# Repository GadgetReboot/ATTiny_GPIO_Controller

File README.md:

# ATTiny_GPIO_Controller
ATTiny x04/x14 GPIO Controller with on-board MCP23017 I2C GPIO Expander

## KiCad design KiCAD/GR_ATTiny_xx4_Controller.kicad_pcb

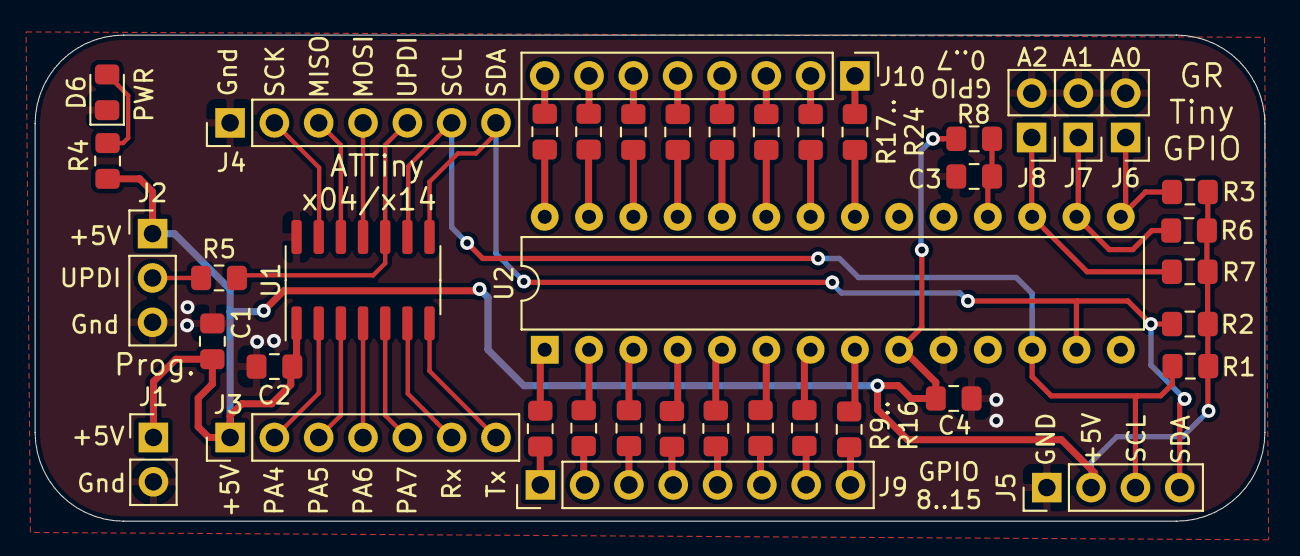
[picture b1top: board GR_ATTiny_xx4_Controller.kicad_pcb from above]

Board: 2 copper layers, 70.5 x 27.9 mm, 41 parts (0 on the bottom side), 52 nets.

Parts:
C1: 1uF; C_0805_2012Metric_Pad1.15x1.40mm_HandSolder
C2, C3, C4: 100nF; C_0805_2012Metric_Pad1.15x1.40mm_HandSolder
D6: Power; LED_0805_2012Metric_Pad1.15x1.40mm_HandSolder
J1, J6, J7, J8: Conn_01x02; PinHeader_1x02_P2.54mm_Vertical
J2: Conn_01x03; PinHeader_1x03_P2.54mm_Vertical
J3, J4: Conn_01x07; PinHeader_1x07_P2.54mm_Vertical
J5: Conn_01x04; PinHeader_1x04_P2.54mm_Vertical
J9, J10: Conn_01x08; PinHeader_1x08_P2.54mm_Vertical
R1, R2, R3, R6, R7, R8: 10K; R_0805_2012Metric_Pad1.15x1.40mm_HandSolder
R4, R5, R9, R10, R11, R12, R13, R14, R15, R16, R17, R18, R19, R20, R21, R22, R23, R24: 1K; R_0805_2012Metric_Pad1.15x1.40mm_HandSolder
U1: ATtiny x04/x14; SOIC-14_3.9x8.7mm_P1.27mm
U2: MCP23017_SP; DIP-28_W7.62mm

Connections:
+5V: C1.1, C2.1, C4.1, J1.1, J2.1, J3.1, J5.2, R1.1, R2.1, R3.2, R4.1, R6.2, R7.2, R8.2, U1.1, U2.9
/MISO: J4.3, U1.12
/MOSI: J4.4, U1.11
/PA4: J3.2, U1.2
/PA5: J3.3, U1.3
/PA6: J3.4, U1.4
/PA7: J3.5, U1.5
/RX_In: J3.6, U1.6
/SCK: J4.2, U1.13
/SCL: J4.6, J5.3, R1.2, U1.9, U2.12
/SDA: J4.7, J5.4, R2.2, U1.8, U2.13
/TX_Out: J3.7, U1.7
/UPDI: J4.5, R5.2, U1.10
GNDREF: C1.2, C2.2, C3.2, C4.2, D6.1, J1.2, J2.3, J4.1, J5.1, J6.2, J7.2, J8.2, U1.14, U2.10
unnamed: C3.1, R8.1, U2.18
unnamed: D6.2, R4.2
unnamed: J2.2, R5.1
unnamed: J6.1, R3.1, U2.15
unnamed: J7.1, R6.1, U2.16
unnamed: J8.1, R7.1, U2.17
unnamed: J9.1, R9.1
unnamed: J9.2, R10.1
unnamed: J9.3, R11.1
unnamed: J9.4, R12.1
unnamed: J9.5, R13.1
unnamed: J9.6, R14.1
unnamed: J9.7, R15.1
unnamed: J9.8, R16.1
unnamed: J10.1, R17.1
unnamed: J10.2, R18.1
unnamed: J10.3, R19.1
unnamed: J10.4, R20.1
unnamed: J10.5, R21.1
unnamed: J10.6, R22.1
unnamed: J10.7, R23.1
unnamed: J10.8, R24.1
unnamed: R9.2, U2.1
unnamed: R10.2, U2.2
unnamed: R11.2, U2.3
unnamed: R12.2, U2.4
unnamed: R13.2, U2.5
unnamed: R14.2, U2.6
unnamed: R15.2, U2.7
unnamed: R16.2, U2.8
unnamed: R17.2, U2.21
unnamed: R18.2, U2.22
unnamed: R19.2, U2.23
unnamed: R20.2, U2.24
unnamed: R21.2, U2.25
unnamed: R22.2, U2.26
unnamed: R23.2, U2.27
unnamed: R24.2, U2.28
